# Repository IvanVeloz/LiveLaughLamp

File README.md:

# Introduction

_Live, Laugh, Lamp_ is a premium LED lamp for the Fluval Liv aquarium. It's inspired by Fluval's own Plant line of LED lights: a lamp with high CRI LEDs, colors tuned for plant growth, and programmable through a smartphone.

### Features
* Powered by USB like the original
* High CRI, above 90, provided by quality Cree LEDs
* Higher power output, e.g. for folks dosing Flourish Excel
* Programmable through HomeAssistant
* Colors are adjustable and dimmable
* Extremely high dynamic range —super fine adjustments in low light settings
* Hacker friendly, design files available
   * Customize with any color Cree XP-G3 or compatible LEDs
   * Every LED gets its own PWM channel
   * Easy firmware setup thanks to ESPHome
 
# Motivation(s)
I bought the first batch of Fluval Liv as soon as it hit the shelves. I loved its aesthetic and its clever filtration system. One thing I wished was for it to have a little timer built into its light. So one thing led to another and I designed this lamp. 

### Having a real night light
But why such a sophisticated lamp for this nano tank? Well, I have Thai Micro Crabs. They are nocturnal and I hardly get to see them. So I was always wishing for a dimmable lamp (with a red light) to watch them on those 3AM water breaks. Many animals don't react much to red light at night, and it doesn't wake you up either. So I wanted this on my bedroom aquarium.

### An enjoyable experience for everybody
Another reason is I have a Fluval Plant 4.0 on a bigger tank. I _love_ running it at 2% brightness in the evenings. I only run its red and warm white LEDs in the evening and it creates a very nice warm white light with pink accents. It's very easy on my eyes. I can tell the fish enjoy it too: the nocturnal ones start to wake up and everybody else starts to wind down.

### Nano tanks deserve advanced equipment
Finally, I just think nano tanks should get the same kind of high quality, advanced equipment that larger tanks get. For example, it's hard to find good nano syphons, nano wave makers, CO₂ systems, etc. This light is my small contribution.

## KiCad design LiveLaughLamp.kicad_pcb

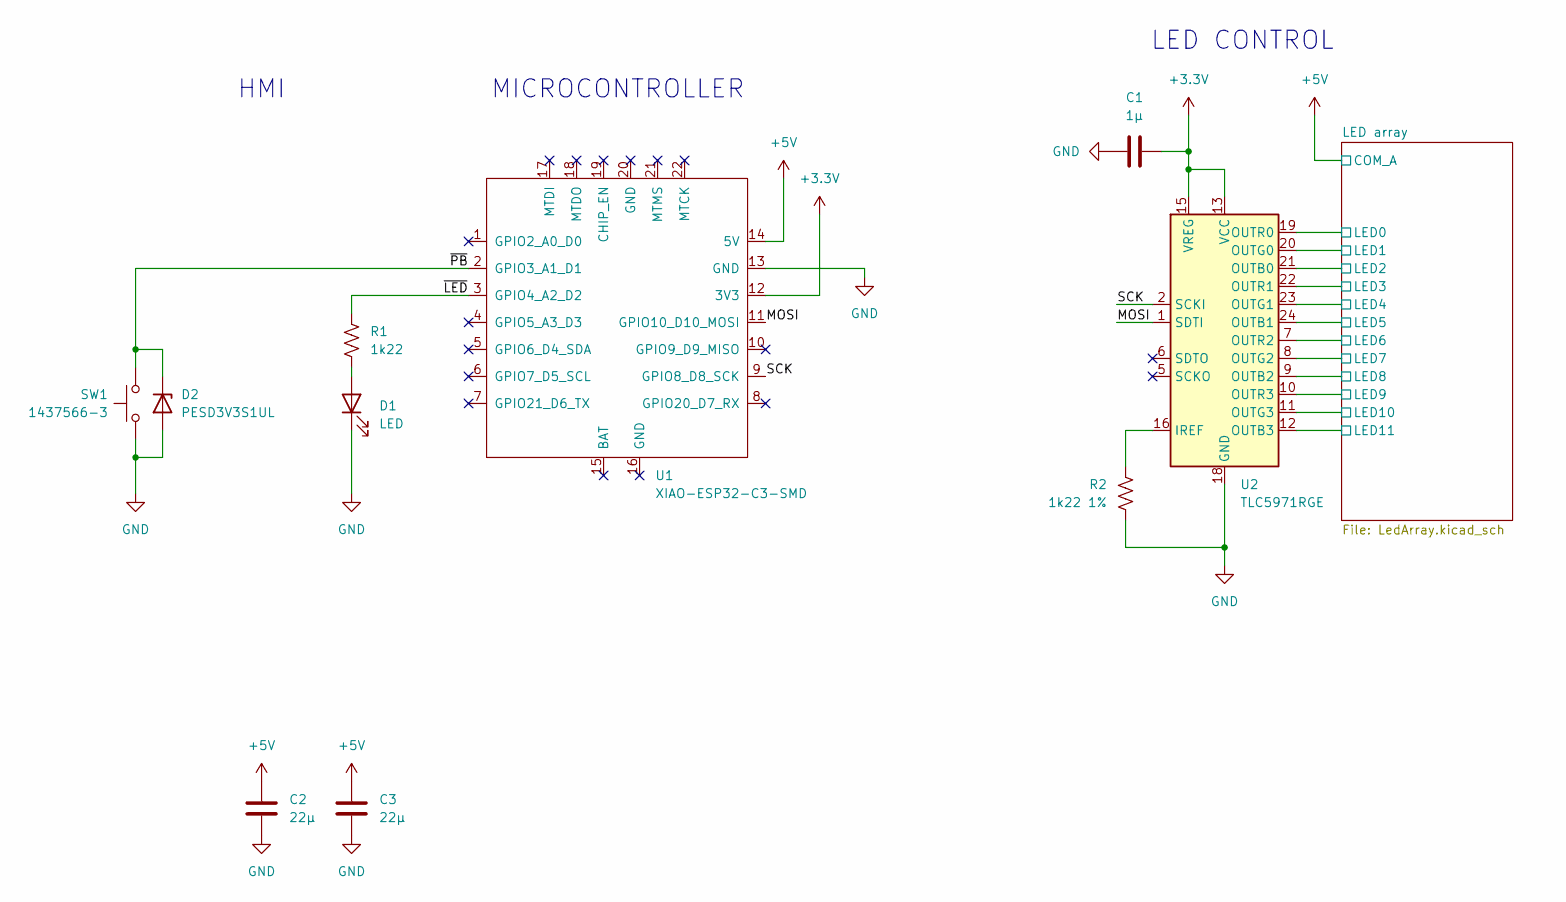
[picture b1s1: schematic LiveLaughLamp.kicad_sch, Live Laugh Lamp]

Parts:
C1: 1µ; C_0402_1005Metric
C2, C3: 22µ; C_0805_2012Metric
D1: LED; LED_0603_1608Metric
D2: PESD3V3S1UL; D_SOD-882
R1: 1k22; R_0402_1005Metric
R2: 1k22 1%; R_0402_1005Metric
SW1: 1437566-3; SW_SPST_B3U-3000P-B
U1: XIAO-ESP32-C3-SMD; XIAO-ESP32C3-SMD
U2: TLC5971RGE; Texas_RGE0024H_VQFN-24-1EP_4x4mm_P0.5mm_EP2.7x2.7mm_Thermal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

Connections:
+3.3V: C1.2, U1.12 (3V3), U2.13 (VCC), U2.15 (VREG)
+5V: C2.1, C3.1, U1.14 (5V); also elsewhere on the board
/LED array/LED0: U2.19 (OUTR0); also elsewhere on the board
/LED array/LED1: U2.20 (OUTG0); also elsewhere on the board
/LED array/LED2: U2.21 (OUTB0); also elsewhere on the board
/LED array/LED3: U2.22 (OUTR1); also elsewhere on the board
/LED array/LED4: U2.23 (OUTG1); also elsewhere on the board
/LED array/LED5: U2.24 (OUTB1); also elsewhere on the board
/LED array/LED6: U2.7 (OUTR2); also elsewhere on the board
/LED array/LED7: U2.8 (OUTG2); also elsewhere on the board
/LED array/LED8: U2.9 (OUTB2); also elsewhere on the board
/LED array/LED9: U2.10 (OUTR3); also elsewhere on the board
/LED array/LED10: U2.11 (OUTG3); also elsewhere on the board
/LED array/LED11: U2.12 (OUTB3); also elsewhere on the board
/MOSI: U1.11 (GPIO10_D10_MOSI), U2.1 (SDTI)
/SCK: U1.9 (GPIO8_D8_SCK), U2.2 (SCKI)
/~LED: R1.1, U1.3 (GPIO4_A2_D2)
/~PB: D2.1 (K), SW1.1, U1.2 (GPIO3_A1_D1)
GND: C1.1, C2.2, C3.2, D1.1 (K), D2.2 (A), R2.2, SW1.2, U1.13 (GND), U2.18 (GND), U2.25 (GND)
unnamed: D1.2 (A), R1.2
unnamed: R2.1, U2.16 (IREF)

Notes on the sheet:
HMI
MICROCONTROLLER
LED CONTROL

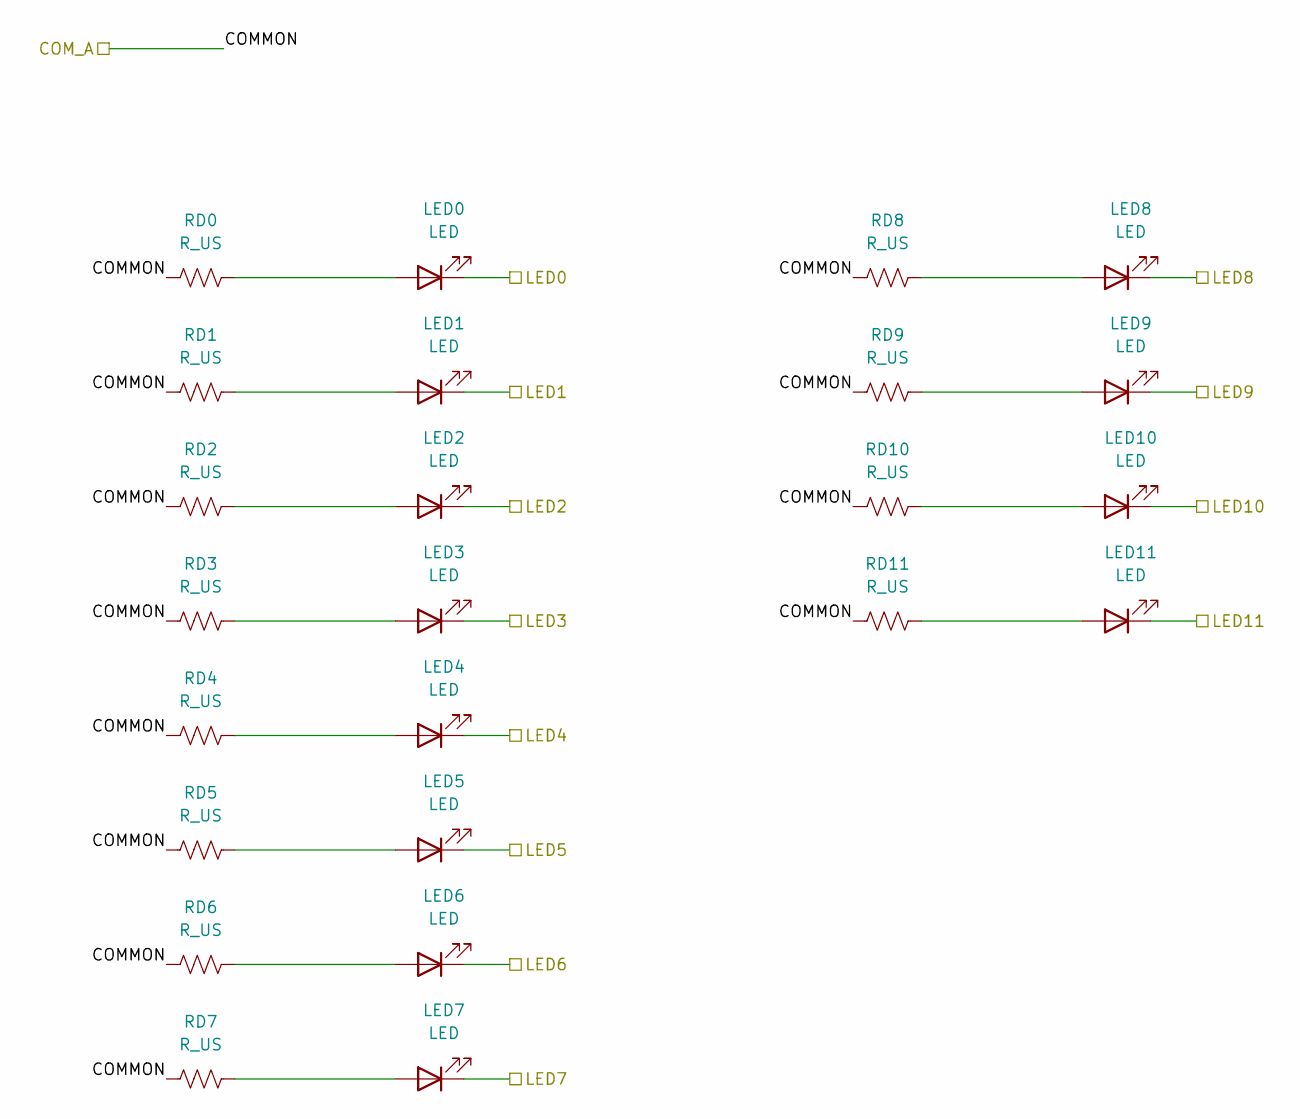
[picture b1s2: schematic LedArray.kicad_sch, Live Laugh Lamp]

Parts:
LED0, LED1, LED2, LED3, LED4, LED5, LED6, LED7, LED8, LED9, LED10, LED11: LED; LED_Cree-XP-G
RD0, RD1, RD2, RD3, RD4, RD5, RD6, RD7, RD8, RD9, RD10, RD11: R_US; R_1206_3216Metric

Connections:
+5V: RD0.2, RD1.2, RD2.2, RD3.2, RD4.2, RD5.2, RD6.2, RD7.2, RD8.2, RD9.2, RD10.2, RD11.2; also elsewhere on the board
/LED array/LED0: LED0.1 (K); also elsewhere on the board
/LED array/LED1: LED1.1 (K); also elsewhere on the board
/LED array/LED2: LED2.1 (K); also elsewhere on the board
/LED array/LED3: LED3.1 (K); also elsewhere on the board
/LED array/LED4: LED4.1 (K); also elsewhere on the board
/LED array/LED5: LED5.1 (K); also elsewhere on the board
/LED array/LED6: LED6.1 (K); also elsewhere on the board
/LED array/LED7: LED7.1 (K); also elsewhere on the board
/LED array/LED8: LED8.1 (K); also elsewhere on the board
/LED array/LED9: LED9.1 (K); also elsewhere on the board
/LED array/LED10: LED10.1 (K); also elsewhere on the board
/LED array/LED11: LED11.1 (K); also elsewhere on the board
unnamed: LED0.2 (A), RD0.1
unnamed: LED1.2 (A), RD1.1
unnamed: LED2.2 (A), RD2.1
unnamed: LED3.2 (A), RD3.1
unnamed: LED4.2 (A), RD4.1
unnamed: LED5.2 (A), RD5.1
unnamed: LED6.2 (A), RD6.1
unnamed: LED7.2 (A), RD7.1
unnamed: LED8.2 (A), RD8.1
unnamed: LED9.2 (A), RD9.1
unnamed: LED10.2 (A), RD10.1
unnamed: LED11.2 (A), RD11.1

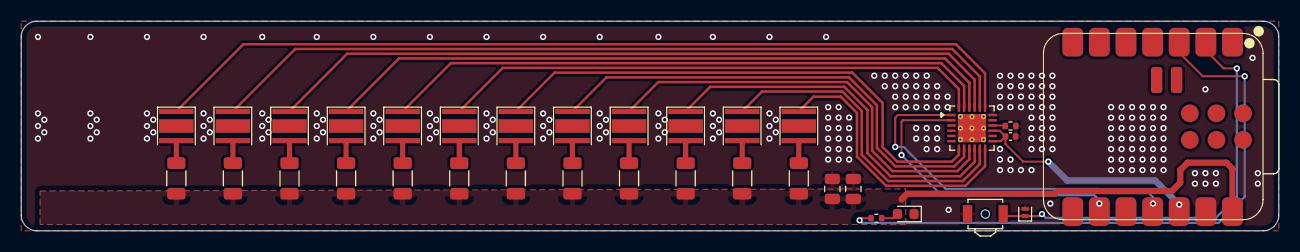
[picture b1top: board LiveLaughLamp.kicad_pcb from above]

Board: 2 copper layers, 120.0 x 20.0 mm, 34 parts (0 on the bottom side), 33 nets.

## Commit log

2026-01-01 Add project with Cree XP-G LEDs and PCA9685 controller
2026-01-01 Add gitignore
2026-01-01 Swap LED controller for TLC5971
2026-01-01 Add thermal sink for Xiao board. Add JLC fabrication metadata.
2026-01-02 Untent thermal vias for Xiao module
2026-01-05 Add production output files
2026-01-17 Change some component values for better sourcing
2026-02-28 Add README content for Live, Laugh, Lamp LED lamp
    Added detailed introduction and features for the Live, Laugh, Lamp LED lamp, including motivations for its design and benefits for nano tanks.

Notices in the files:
LiveLaughLamp.kicad_pcb:
© 2025 Ivan Veloz
